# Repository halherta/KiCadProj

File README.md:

This is a Repo of some of My PCB Designs. More to follow...

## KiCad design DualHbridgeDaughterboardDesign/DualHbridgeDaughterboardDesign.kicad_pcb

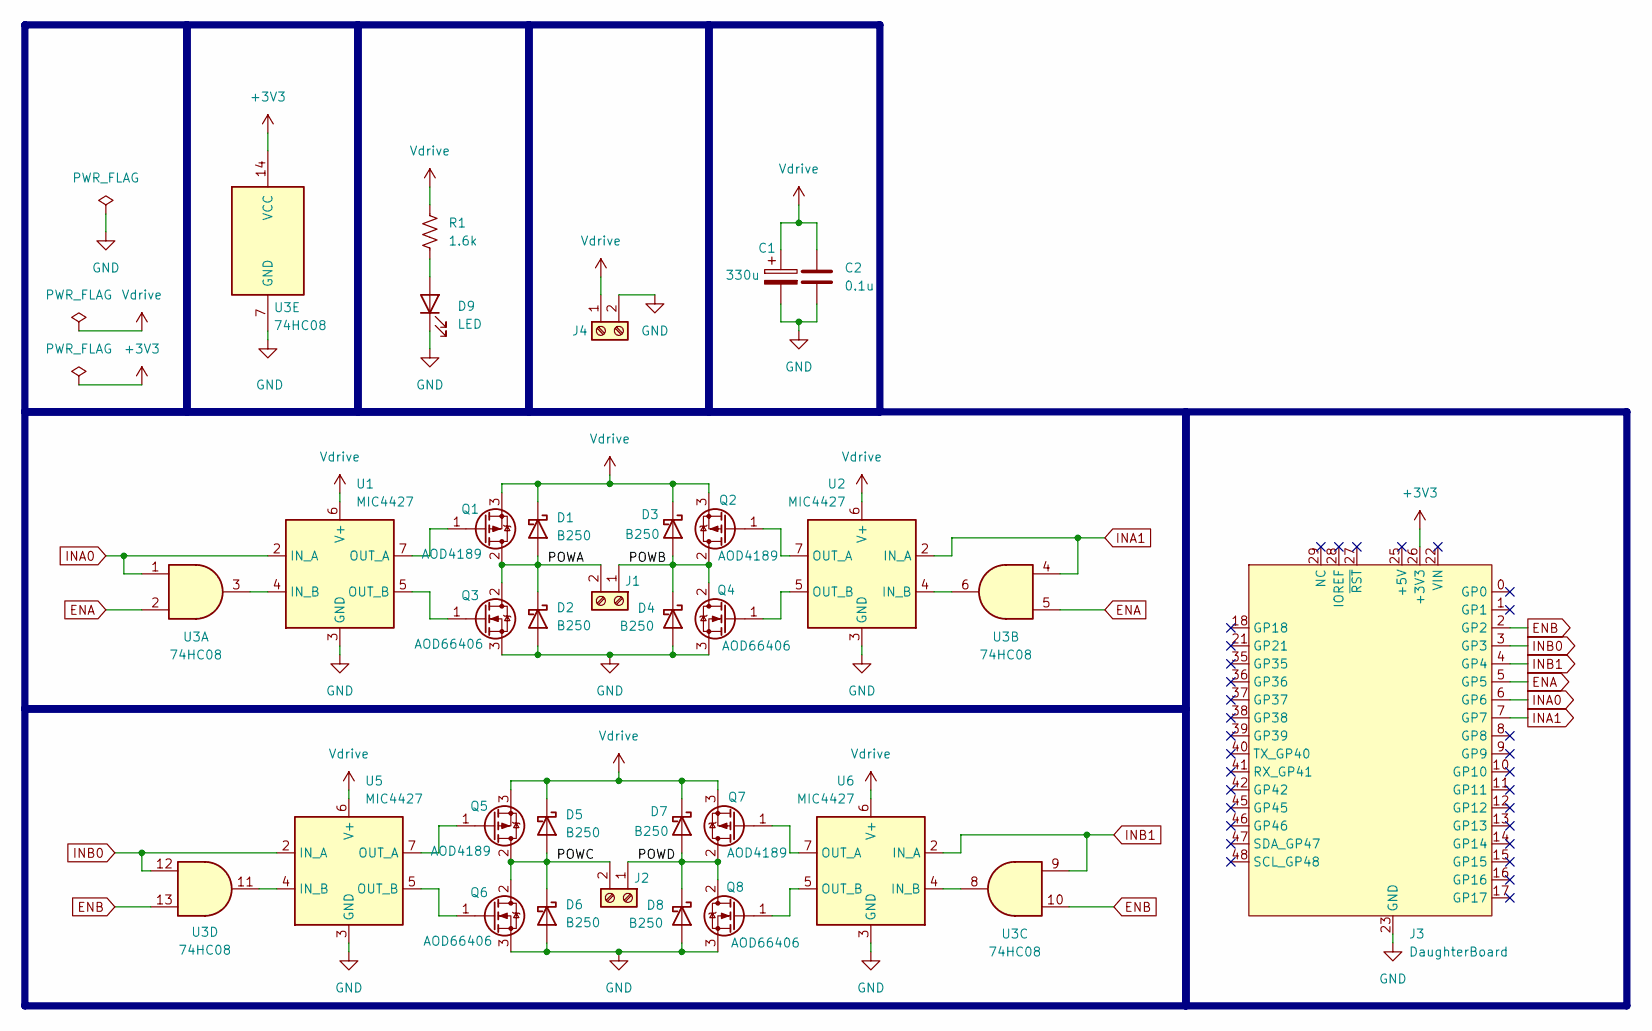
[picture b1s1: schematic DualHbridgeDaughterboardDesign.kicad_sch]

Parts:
C1: 330u; CP_Elec_8x10
C2: 0.1u; C_1206_3216Metric_Pad1.33x1.80mm_HandSolder
D1, D2, D3, D4, D5, D6, D7, D8: B250; D_SMB
D9: LED; LED_1206_3216Metric_Pad1.42x1.75mm_HandSolder
J1, J2, J4: Screw_Terminal_01x02; TerminalBlock_Altech_AK300-2_P5.00mm
J3: DaughterBoard; DaughterBoardTemplate
Q1, Q2, Q5, Q7: AOD4189; TO-252-2
Q3, Q4, Q6, Q8: AOD66406; TO-252-2
R1: 1.6k; R_1206_3216Metric_Pad1.30x1.75mm_HandSolder
U1, U2, U5, U6: MIC4427; SO-8_3.9x4.9mm_P1.27mm
U3: 74HC08; SO-14_3.9x8.65mm_P1.27mm

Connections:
+3V3: J3.26 (+3V3), J3.32 (+3V3), U3.14 (VCC)
/POWA: D1.2 (A), D2.1 (K), J1.2, Q1.2 (D), Q3.2 (D)
/POWB: D3.2 (A), D4.1 (K), J1.1, Q2.2 (D), Q4.2 (D)
/POWC: D5.2 (A), D6.1 (K), J2.2, Q5.2 (D), Q6.2 (D)
/POWD: D7.2 (A), D8.1 (K), J2.1, Q7.2 (D), Q8.2 (D)
ENA: J3.5 (GP5), U3.2, U3.5
ENB: J3.2 (GP2), U3.10, U3.13
GND: C1.2, C2.2, D2.2 (A), D4.2 (A), D6.2 (A), D8.2 (A), D9.1 (K), J3.23 (GND), J3.24 (GND), J3.30 (GND), J4.2, Q3.3 (S), Q4.3 (S), Q6.3 (S), Q8.3 (S), U1.3 (GND), U2.3 (GND), U3.7 (GND), U5.3 (GND), U6.3 (GND)
INA0: J3.6 (GP6), U1.2 (IN_A), U3.1
INA1: J3.7 (GP7), U2.2 (IN_A), U3.4
INB0: J3.3 (GP3), U3.12, U5.2 (IN_A)
INB1: J3.4 (GP4), U3.9, U6.2 (IN_A)
unnamed: D9.2 (A), R1.2
unnamed: Q1.1 (G), U1.7 (OUT_A)
unnamed: Q2.1 (G), U2.7 (OUT_A)
unnamed: Q3.1 (G), U1.5 (OUT_B)
unnamed: Q4.1 (G), U2.5 (OUT_B)
unnamed: Q5.1 (G), U5.7 (OUT_A)
unnamed: Q6.1 (G), U5.5 (OUT_B)
unnamed: Q7.1 (G), U6.7 (OUT_A)
unnamed: Q8.1 (G), U6.5 (OUT_B)
unnamed: U1.4 (IN_B), U3.3
unnamed: U2.4 (IN_B), U3.6
unnamed: U3.11, U5.4 (IN_B)
unnamed: U3.8, U6.4 (IN_B)
Vdrive: C1.1, C2.1, D1.1 (K), D3.1 (K), D5.1 (K), D7.1 (K), J4.1, Q1.3 (S), Q2.3 (S), Q5.3 (S), Q7.3 (S), R1.1, U1.6 (V+), U2.6 (V+), U5.6 (V+), U6.6 (V+)

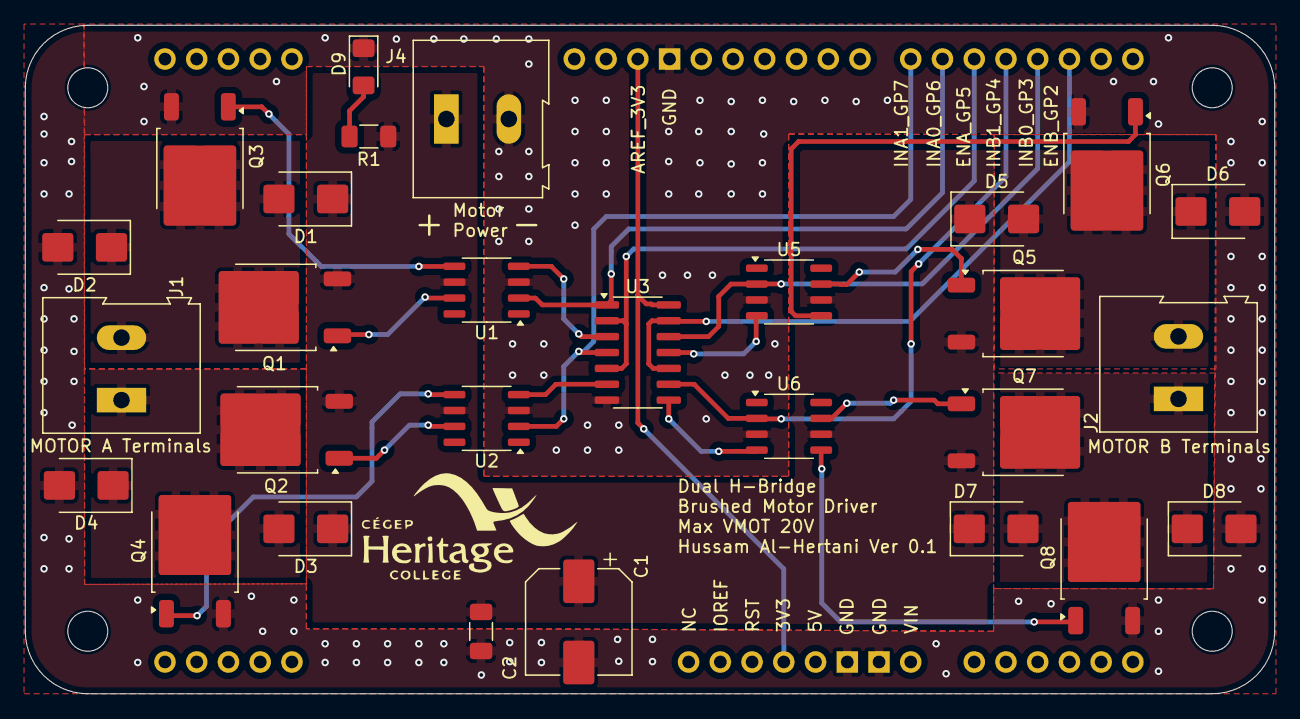
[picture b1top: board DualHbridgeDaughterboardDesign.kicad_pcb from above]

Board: 2 copper layers, 100.0 x 53.5 mm, 29 parts (0 on the bottom side), 26 nets.

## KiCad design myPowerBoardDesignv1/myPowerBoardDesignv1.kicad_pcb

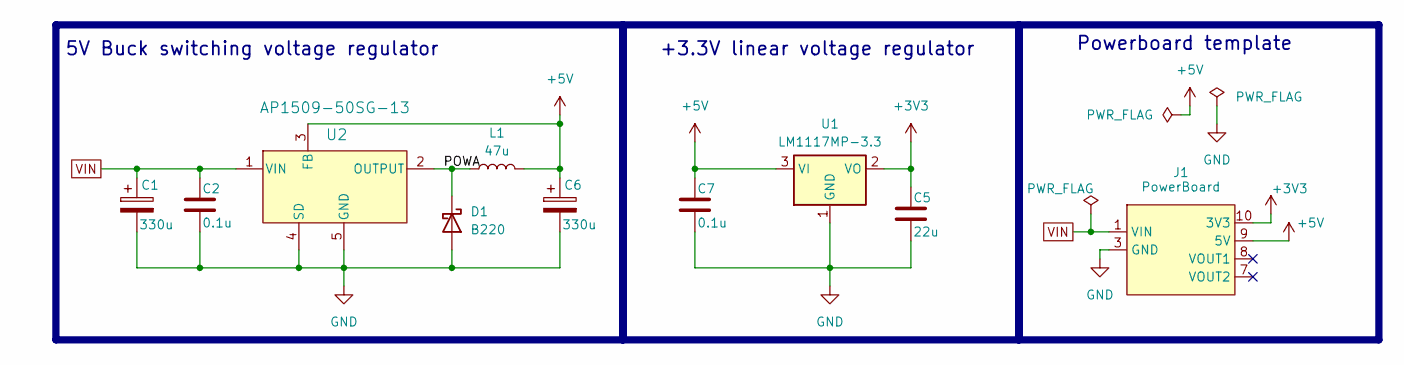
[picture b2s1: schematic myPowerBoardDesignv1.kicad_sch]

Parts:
C1, C6: 330u; CP_Elec_8x10.5
C2, C7: 0.1u; C_1206_3216Metric_Pad1.33x1.80mm_HandSolder
C5: 22u; C_1206_3216Metric_Pad1.33x1.80mm_HandSolder
D1: B220; D_SMB
J1: PowerBoard; PowerBoardTemplate
L1: 47u; L_Bourns-SRN1060
U1: LM1117MP-3.3; SOT-223-3_TabPin2
U2: AP1509-50SG-13; SOP-8_3.9x4.9mm_P1.27mm

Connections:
+3V3: C5.2, J1.10 (3V3), U1.2 (VO)
+5V: C6.1, C7.2, J1.9 (5V), L1.2, U1.3 (VI), U2.3 (FB)
/POWA: D1.1 (K), L1.1, U2.2 (OUTPUT)
GND: C1.2, C2.1, C5.1, C6.2, C7.1, D1.2 (A), J1.3 (GND), J1.4 (GND), J1.5 (GND), J1.6 (GND), U1.1 (GND), U2.4 (SD), U2.5 (GND), U2.6 (GND), U2.7 (GND), U2.8 (GND)
VIN: C1.1, C2.2, J1.1 (VIN), J1.2 (VIN), U2.1 (VIN)

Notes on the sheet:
5V Buck switching voltage regulator
Powerboard template
+3.3V linear voltage regulator

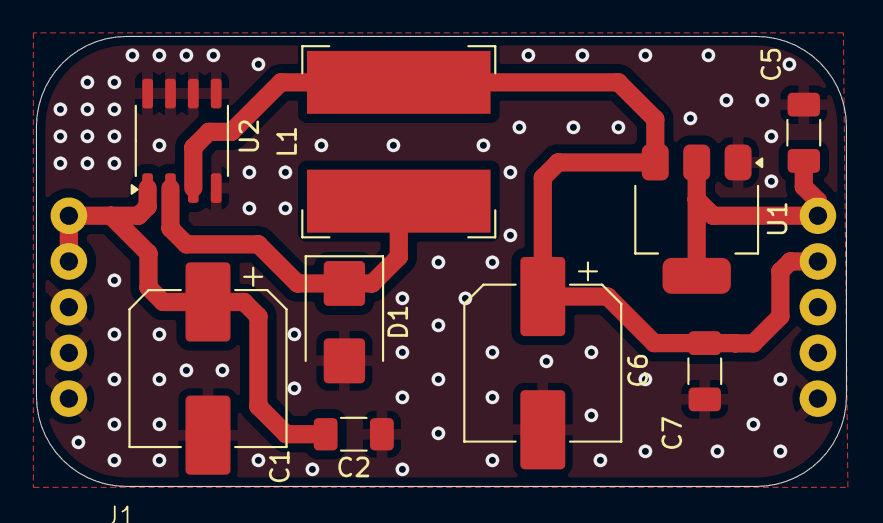
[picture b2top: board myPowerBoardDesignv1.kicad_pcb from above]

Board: 2 copper layers, 45.0 x 25.0 mm, 10 parts (0 on the bottom side), 5 nets.

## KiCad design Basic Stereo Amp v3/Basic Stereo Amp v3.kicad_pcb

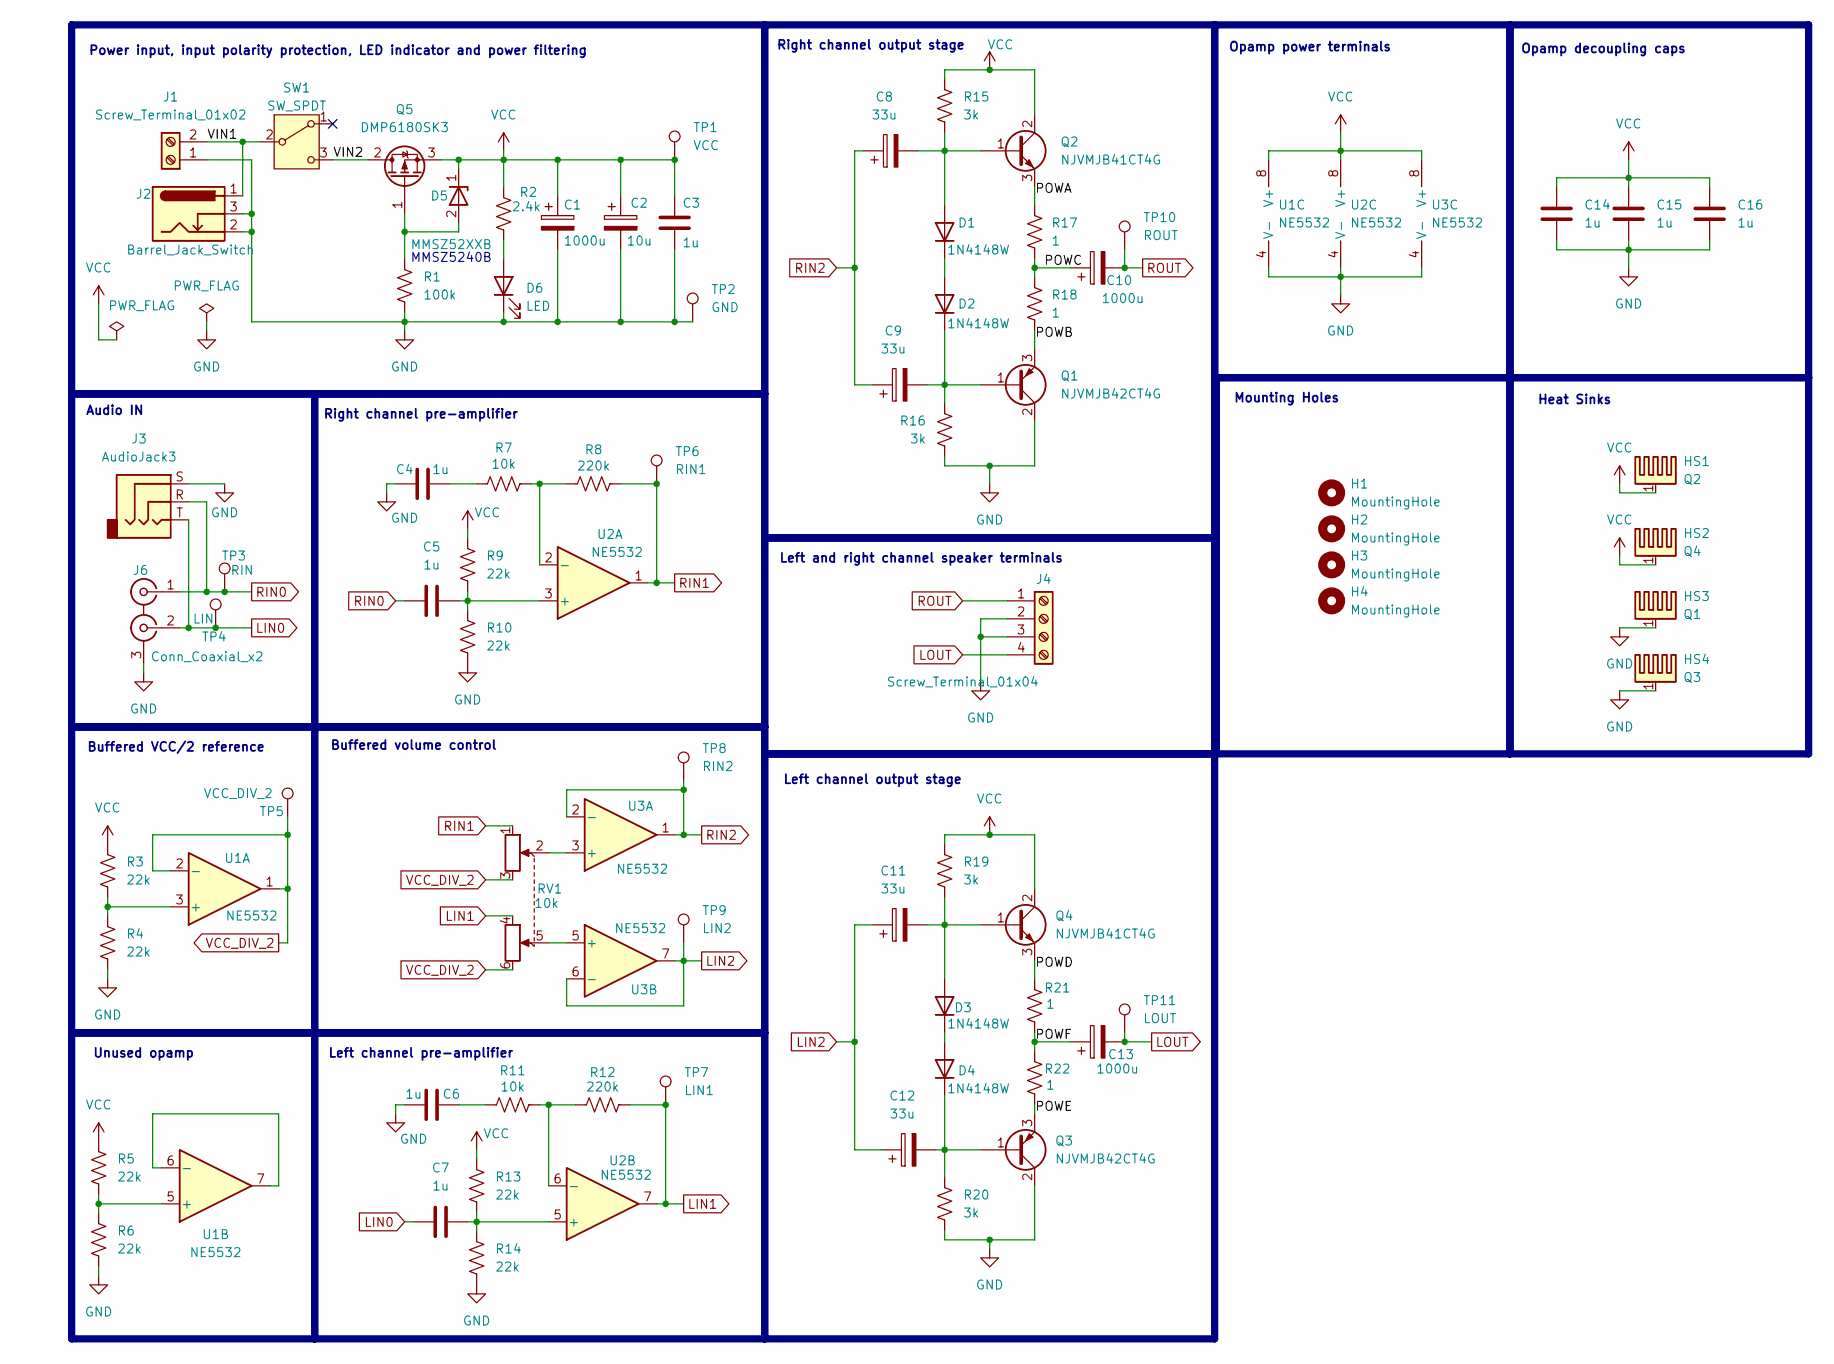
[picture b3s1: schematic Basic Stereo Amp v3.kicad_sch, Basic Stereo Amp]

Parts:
C1, C10, C13: 1000u; CP_Elec_16x17.5
C2: 10u; CP_Elec_5x5.3
C3, C4, C5, C6, C7, C14, C15, C16: 1u; C_1206_3216Metric_Pad1.33x1.80mm_HandSolder
C8, C9, C11, C12: 33u; C_Elec_6.3x5.4
D1, D2, D3, D4: 1N4148W; D_SOD-123
D5: MMSZ52XXB; D_SOD-123
D6: LED; LED_1206_3216Metric_Pad1.42x1.75mm_HandSolder
H1, H2, H3, H4: MountingHole; MountingHole_3.2mm_M3_ISO7380
HS1: Q2; Heatsink_AAVID_573300D00010G_TO-263
HS2: Q4; Heatsink_AAVID_573300D00010G_TO-263
HS3: Q1; Heatsink_AAVID_573300D00010G_TO-263
HS4: Q3; Heatsink_AAVID_573300D00010G_TO-263
J1: Screw_Terminal_01x02; TerminalBlock_Altech_AK300-2_P5.00mm
J2: Barrel_Jack_Switch; BarrelJack_CUI_PJ-102AH_Horizontal
J3: AudioJack3; Jack_3.5mm_CUI_SJ1-3533NG_Horizontal
J4: Screw_Terminal_01x04; TerminalBlock_Altech_AK300-4_P5.00mm
J6: Conn_Coaxial_x2; RCJ-2223
Q1, Q3: NJVMJB42CT4G; TO-263-2
Q2, Q4: NJVMJB41CT4G; TO-263-2
Q5: DMP6180SK3; TO-252-2
R1: 100k; R_1206_3216Metric_Pad1.30x1.75mm_HandSolder
R2: 2.4k; R_1206_3216Metric_Pad1.30x1.75mm_HandSolder
R3, R4, R5, R6, R9, R10, R13, R14: 22k; R_1206_3216Metric_Pad1.30x1.75mm_HandSolder
R7, R11: 10k; R_1206_3216Metric_Pad1.30x1.75mm_HandSolder
R8, R12: 220k; R_1206_3216Metric_Pad1.30x1.75mm_HandSolder
R15, R16, R19, R20: 3k; R_1206_3216Metric_Pad1.30x1.75mm_HandSolder
R17, R18, R21, R22: 1; R_2512_6332Metric_Pad1.40x3.35mm_HandSolder
RV1: 10k; PTD902-2015K-B103
SW1: SW_SPDT; SW_E-Switch_EG1224_SPDT_Angled
TP1: VCC; TestPoint_THTPad_D2.0mm_Drill1.0mm
TP2: GND; TestPoint_THTPad_D2.0mm_Drill1.0mm
TP3: RIN; TestPoint_THTPad_D2.0mm_Drill1.0mm
TP4: LIN; TestPoint_THTPad_D2.0mm_Drill1.0mm
TP5: VCC_DIV_2; TestPoint_THTPad_D2.0mm_Drill1.0mm
TP6: RIN1; TestPoint_THTPad_D2.0mm_Drill1.0mm
TP7: LIN1; TestPoint_THTPad_D2.0mm_Drill1.0mm
TP8: RIN2; TestPoint_THTPad_D2.0mm_Drill1.0mm
TP9: LIN2; TestPoint_THTPad_D2.0mm_Drill1.0mm
TP10: ROUT; TestPoint_THTPad_D2.0mm_Drill1.0mm
TP11: LOUT; TestPoint_THTPad_D2.0mm_Drill1.0mm
U1, U2, U3: NE5532; SOIC-8_3.9x4.9mm_P1.27mm

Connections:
/POWA: Q2.3 (E), R17.1
/POWB: Q1.3 (E), R18.2
/POWC: C10.1, R17.2, R18.1
/POWD: Q4.3 (E), R21.1
/POWE: Q3.3 (E), R22.2
/POWF: C13.1, R21.2, R22.1
/VIN1: J1.2, J2.1, SW1.2 (B)
/VIN2: Q5.2 (D), SW1.3 (C)
GND: C1.2, C2.2, C3.2, C4.2, C6.2, C14.2, C15.2, C16.2, D6.1 (K), HS3.1, HS4.1, J1.1, J2.2, J2.3, J3.S, J4.2, J4.3, J6.3 (EXT), Q1.2 (C), Q3.2 (C), R1.2, R4.1, R6.1, R10.1, R14.1, R16.2, R20.2, TP2.1, U1.4 (V-), U2.4 (V-), U3.4 (V-)
LIN0: C7.2, J3.T, J6.2 (IN2), TP4.1
LIN1: R12.2, RV1.4, TP7.1, U2.7
LIN2: C11.1, C12.1, TP9.1, U3.6 (-), U3.7
LOUT: C13.2, J4.4, TP11.1
unnamed: C4.1, R7.1
unnamed: C6.1, R11.1
unnamed: C8.2, D1.2 (A), Q2.1 (B), R15.2
unnamed: D1.1 (K), D2.2 (A)
unnamed: C9.2, D2.1 (K), Q1.1 (B), R16.1
unnamed: C11.2, D3.2 (A), Q4.1 (B), R19.2
unnamed: D3.1 (K), D4.2 (A)
unnamed: C12.2, D4.1 (K), Q3.1 (B), R20.1
unnamed: D5.2 (A), Q5.1 (G), R1.1
unnamed: D6.2 (A), R2.2
unnamed: R3.1, R4.2, U1.3 (+)
unnamed: R5.1, R6.2, U1.5 (+)
unnamed: U1.6 (-), U1.7
unnamed: C5.1, R9.1, R10.2, U2.3 (+)
unnamed: R7.2, R8.1, U2.2 (-)
unnamed: C7.1, R13.1, R14.2, U2.5 (+)
unnamed: R11.2, R12.1, U2.6 (-)
unnamed: RV1.2, U3.3 (+)
unnamed: RV1.5, U3.5 (+)
RIN0: C5.2, J3.R, J6.1 (IN1), TP3.1
RIN1: R8.2, RV1.1, TP6.1, U2.1
RIN2: C8.1, C9.1, TP8.1, U3.1, U3.2 (-)
ROUT: C10.2, J4.1, TP10.1
VCC: C1.1, C2.1, C3.1, C14.1, C15.1, C16.1, D5.1 (K), HS1.1, HS2.1, Q2.2 (C), Q4.2 (C), Q5.3 (S), R2.1, R3.2, R5.2, R9.2, R13.2, R15.1, R19.1, TP1.1, U1.8 (V+), U2.8 (V+), U3.8 (V+)
VCC_DIV_2: RV1.3, RV1.6, TP5.1, U1.1, U1.2 (-)

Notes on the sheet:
Left channel output stage
Audio IN
MMSZ5240B
Heat Sinks
Opamp decoupling caps
Mounting Holes
Buffered volume control
Opamp power terminals
Right channel pre-amplifier
Buffered VCC/2 reference
Unused opamp
Right channel output stage
Left and right channel speaker terminals
Left channel pre-amplifier
Power input, input polarity protection, LED indicator and power filtering

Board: 2 copper layers, 78 parts (0 on the bottom side), 38 nets, no tracks yet.

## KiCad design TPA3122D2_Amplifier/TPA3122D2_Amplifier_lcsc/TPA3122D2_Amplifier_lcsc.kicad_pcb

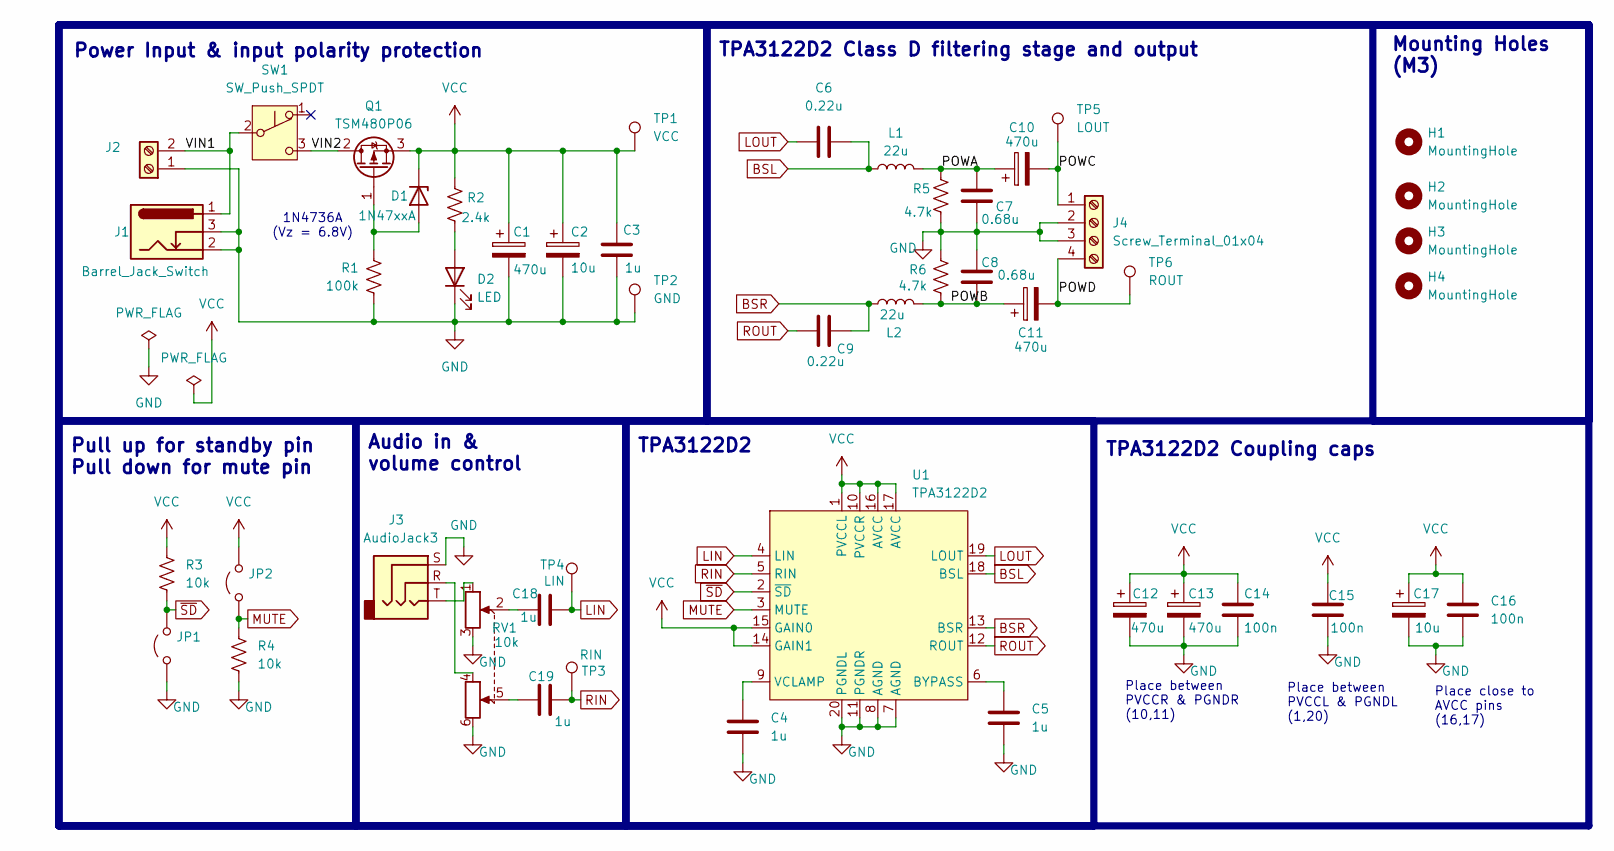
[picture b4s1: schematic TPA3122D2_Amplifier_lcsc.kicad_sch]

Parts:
C1, C10, C11, C12, C13: 470u; CP_Radial_D10.0mm_P5.00mm
C2, C17: 10u; CP_Radial_D5.0mm_P2.50mm
C3, C4, C5, C18, C19: 1u; C_Disc_D4.3mm_W1.9mm_P5.00mm
C6, C9: 0.22u; C_Disc_D4.3mm_W1.9mm_P5.00mm
C7, C8: 0.68u; C_Disc_D4.3mm_W1.9mm_P5.00mm
C14, C15, C16: 100n; C_Disc_D4.3mm_W1.9mm_P5.00mm
D1: 1N47xxA; D_DO-41_SOD81_P10.16mm_Horizontal
D2: LED; LED_D5.0mm
H1, H2, H3, H4: MountingHole; MountingHole_3.2mm_M3
J1: Barrel_Jack_Switch; BarrelJack_CUI_PJ-102AH_Horizontal
J2: Screw_Terminal_01x02; TerminalBlock_Altech_AK300-2_P5.00mm
J3: AudioJack3; Jack_3.5mm_CUI_SJ1-3533NG_Horizontal
J4: Screw_Terminal_01x04; TerminalBlock_Altech_AK300-4_P5.00mm
JP1, JP2: Jumper_2_Open; PinHeader_1x02_P2.54mm_Vertical
L1, L2: 22u; L_Radial_D10.0mm_P5.00mm_Fastron_07M
Q1: TSM480P06; TO-251-3_Vertical
R1: 100k; R_Axial_DIN0207_L6.3mm_D2.5mm_P10.16mm_Horizontal
R2: 2.4k; R_Axial_DIN0207_L6.3mm_D2.5mm_P10.16mm_Horizontal
R3, R4: 10k; R_Axial_DIN0207_L6.3mm_D2.5mm_P10.16mm_Horizontal
R5, R6: 4.7k; R_Axial_DIN0207_L6.3mm_D2.5mm_P10.16mm_Horizontal
RV1: 10k; PTD902-2015K-B103
SW1: SW_Push_SPDT; SW_E-Switch_EG1224_SPDT_Angled
TP1: VCC; TestPoint_THTPad_D2.0mm_Drill1.0mm
TP2: GND; TestPoint_THTPad_D2.0mm_Drill1.0mm
TP3: RIN; TestPoint_THTPad_D2.0mm_Drill1.0mm
TP4: LIN; TestPoint_THTPad_D2.0mm_Drill1.0mm
TP5: LOUT; TestPoint_THTPad_D2.0mm_Drill1.0mm
TP6: ROUT; TestPoint_THTPad_D2.0mm_Drill1.0mm
U1: TPA3122D2; DIP-20_W7.62mm_LongPads

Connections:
/POWA: C7.1, C10.1, L1.2, R5.1
/POWB: C8.2, C11.1, L2.2, R6.2
/POWC: C10.2, J4.1, TP5.1
/POWD: C11.2, J4.4, TP6.1
/VIN1: J1.1, J2.2, SW1.2 (B)
/VIN2: Q1.2 (D), SW1.3 (C)
BSL: C6.1, L1.1, U1.18 (BSL)
BSR: C9.1, L2.1, U1.13 (BSR)
GND: C1.2, C2.2, C3.2, C4.2, C5.2, C7.2, C8.1, C12.2, C13.2, C14.2, C15.2, C16.2, C17.2, D2.1 (K), J1.2, J1.3, J2.1, J3.S, J4.2, J4.3, JP1.1 (A), R1.2, R4.2, R5.2, R6.1, RV1.3, RV1.6, TP2.1, U1.7 (AGND), U1.8 (AGND), U1.11 (PGNDR), U1.20 (PGNDL)
LIN: C18.2, TP4.1, U1.4 (LIN)
LOUT: C6.2, U1.19 (LOUT)
MUTE: JP2.1 (A), R4.1, U1.3 (MUTE)
unnamed: C18.1, RV1.2
unnamed: C19.1, RV1.5
unnamed: D1.2 (A), Q1.1 (G), R1.1
unnamed: D2.2 (A), R2.2
unnamed: J3.R, RV1.4
unnamed: J3.T, RV1.1
unnamed: C5.1, U1.6 (BYPASS)
unnamed: C4.1, U1.9 (VCLAMP)
RIN: C19.2, TP3.1, U1.5 (RIN)
ROUT: C9.2, U1.12 (ROUT)
VCC: C1.1, C2.1, C3.1, C12.1, C13.1, C14.1, C15.1, C16.1, C17.1, D1.1 (K), JP2.2 (B), Q1.3 (S), R2.1, R3.1, TP1.1, U1.1 (PVCCL), U1.10 (PVCCR), U1.14 (GAIN1), U1.15 (GAIN0), U1.16 (AVCC), U1.17 (AVCC)
~SD: JP1.2 (B), R3.2, U1.2 (~SD)

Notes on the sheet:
1N4736A (Vz = 6.8V)
Audio in & volume control
Power Input & input polarity protection
TPA3122D2 Coupling caps
Mounting Holes (M3)
TPA3122D2
Place between PVCCR & PGNDR (10,11)
Place between PVCCL & PGNDL (1,20)
Place close to AVCC pins (16,17)
TPA3122D2 Class D filtering stage and output
Pull up for standby pin Pull down for mute pin

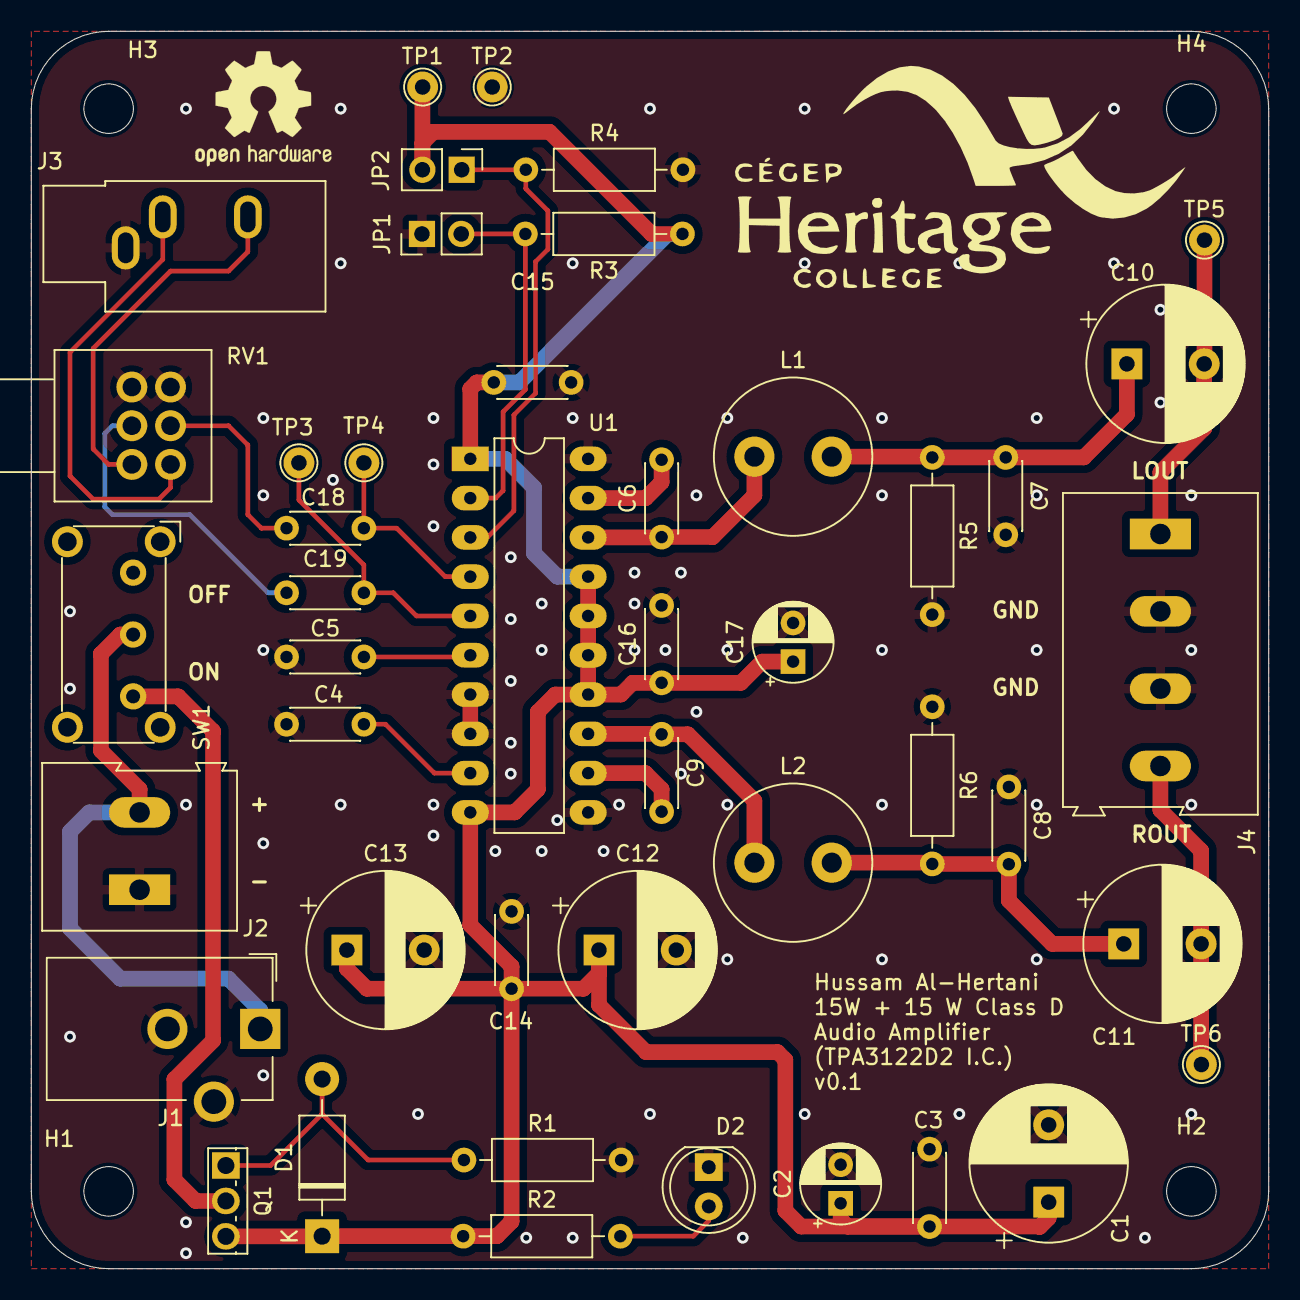
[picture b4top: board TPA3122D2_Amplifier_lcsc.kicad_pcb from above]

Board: 2 copper layers, 80.0 x 80.0 mm, 49 parts (0 on the bottom side), 24 nets.

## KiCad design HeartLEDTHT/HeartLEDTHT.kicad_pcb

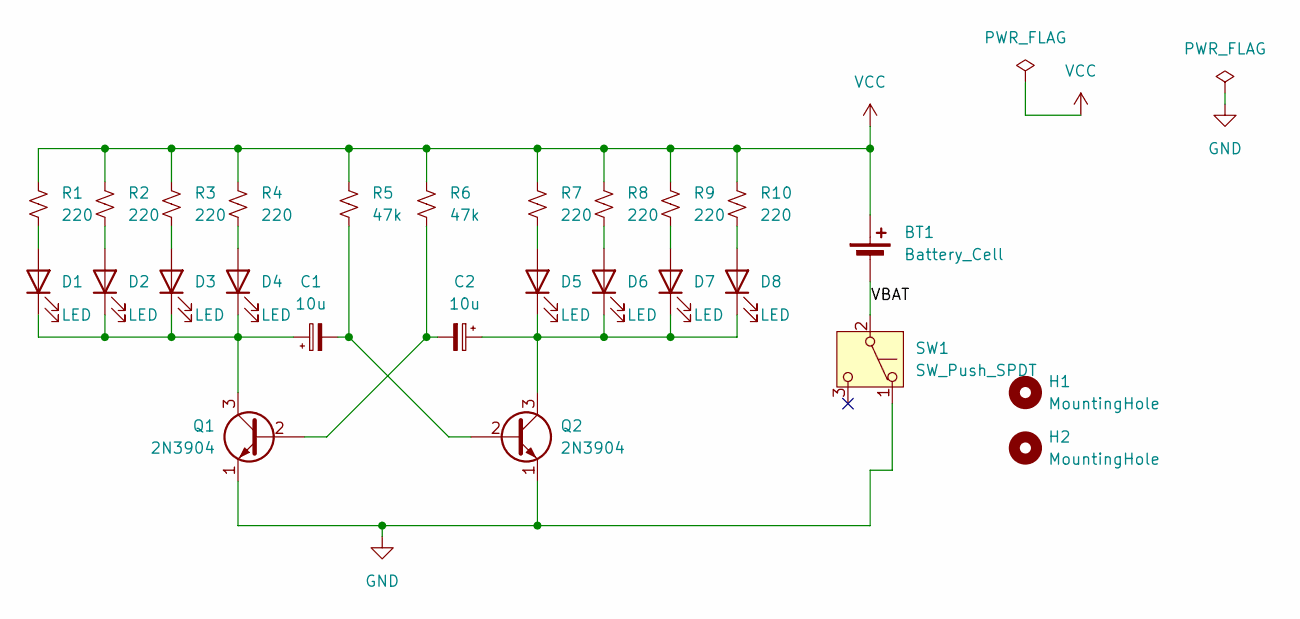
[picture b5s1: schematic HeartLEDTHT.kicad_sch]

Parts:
BT1: Battery_Cell; BatteryHolder_Keystone_3002_1x2032
C1, C2: 10u; CP_Radial_D5.0mm_P2.00mm
D1, D2, D3, D4, D5, D6, D7, D8: LED; LED_D5.0mm
H1, H2: MountingHole; MountingHole_4.3mm_M4
Q1, Q2: 2N3904; TO-92_Inline
R1, R2, R3, R4, R7, R8, R9, R10: 220; R_Axial_DIN0207_L6.3mm_D2.5mm_P10.16mm_Horizontal
R5, R6: 47k; R_Axial_DIN0207_L6.3mm_D2.5mm_P10.16mm_Horizontal
SW1: SW_Push_SPDT; SW_SPDT_CK_JS102011SAQN

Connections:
/VBAT: BT1.2 (-), SW1.2 (B)
GND: Q1.1 (E), Q2.1 (E), SW1.1 (A)
unnamed: D1.2 (A), R1.2
unnamed: C1.1, D1.1 (K), D2.1 (K), D3.1 (K), D4.1 (K), Q1.3 (C)
unnamed: D2.2 (A), R2.2
unnamed: D3.2 (A), R3.2
unnamed: D4.2 (A), R4.2
unnamed: D5.2 (A), R7.2
unnamed: C2.1, D5.1 (K), D6.1 (K), D7.1 (K), D8.1 (K), Q2.3 (C)
unnamed: D6.2 (A), R8.2
unnamed: D7.2 (A), R9.2
unnamed: D8.2 (A), R10.2
unnamed: C2.2, Q1.2 (B), R6.2
unnamed: C1.2, Q2.2 (B), R5.2
VCC: BT1.1 (+), R1.1, R2.1, R3.1, R4.1, R5.1, R6.1, R7.1, R8.1, R9.1, R10.1

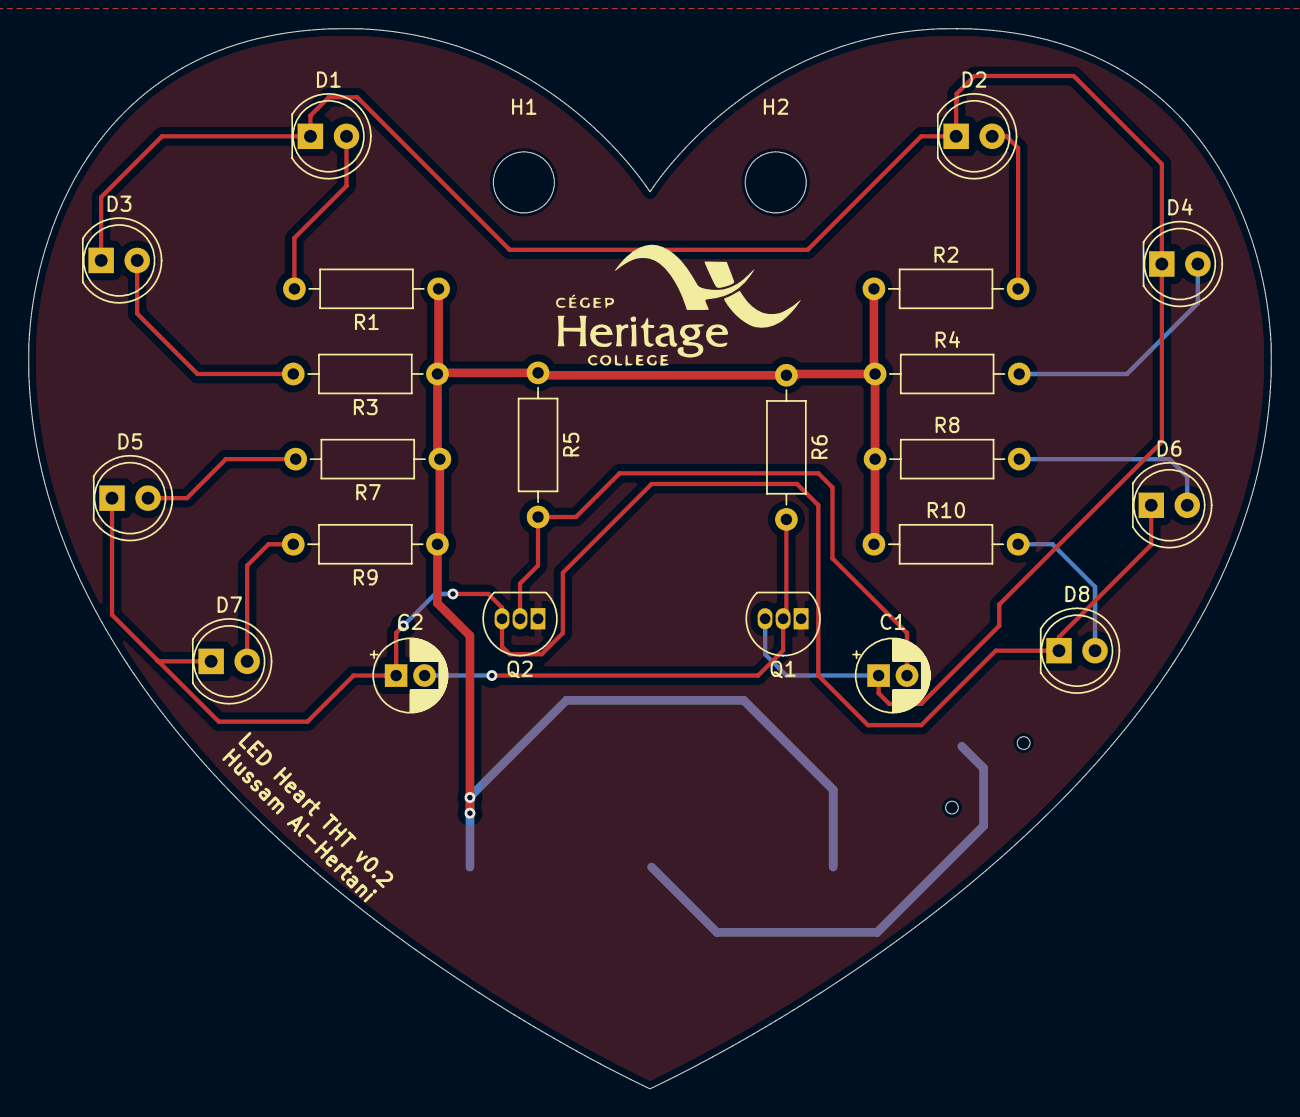
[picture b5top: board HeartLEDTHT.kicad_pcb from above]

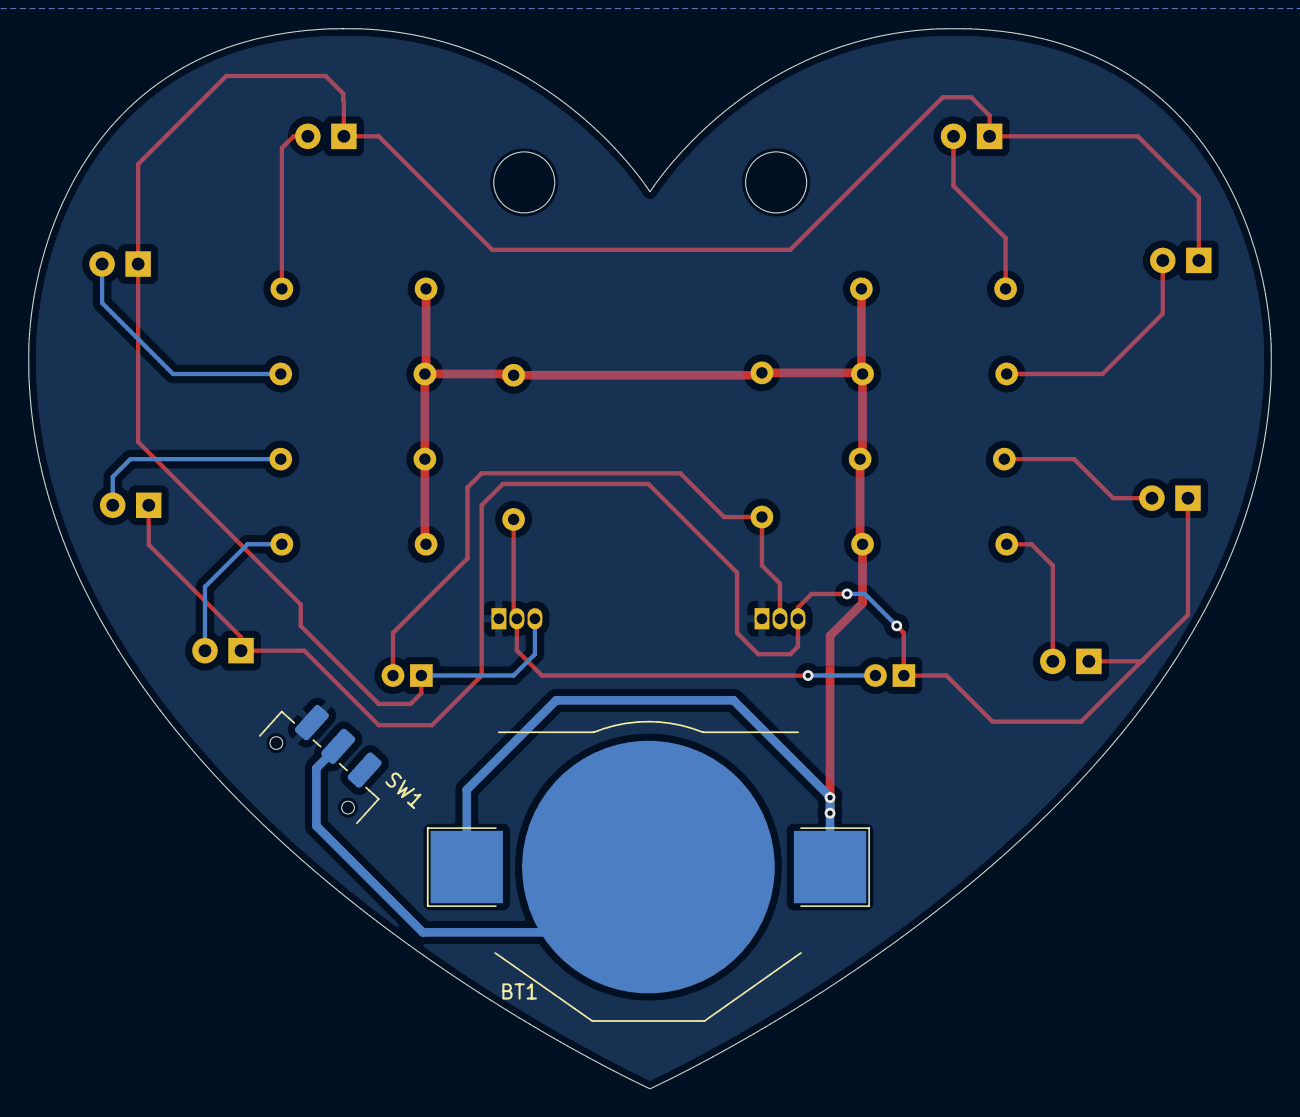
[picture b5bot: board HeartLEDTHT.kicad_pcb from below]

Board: 2 copper layers, 87.6 x 74.7 mm, 26 parts (2 on the bottom side), 15 nets.

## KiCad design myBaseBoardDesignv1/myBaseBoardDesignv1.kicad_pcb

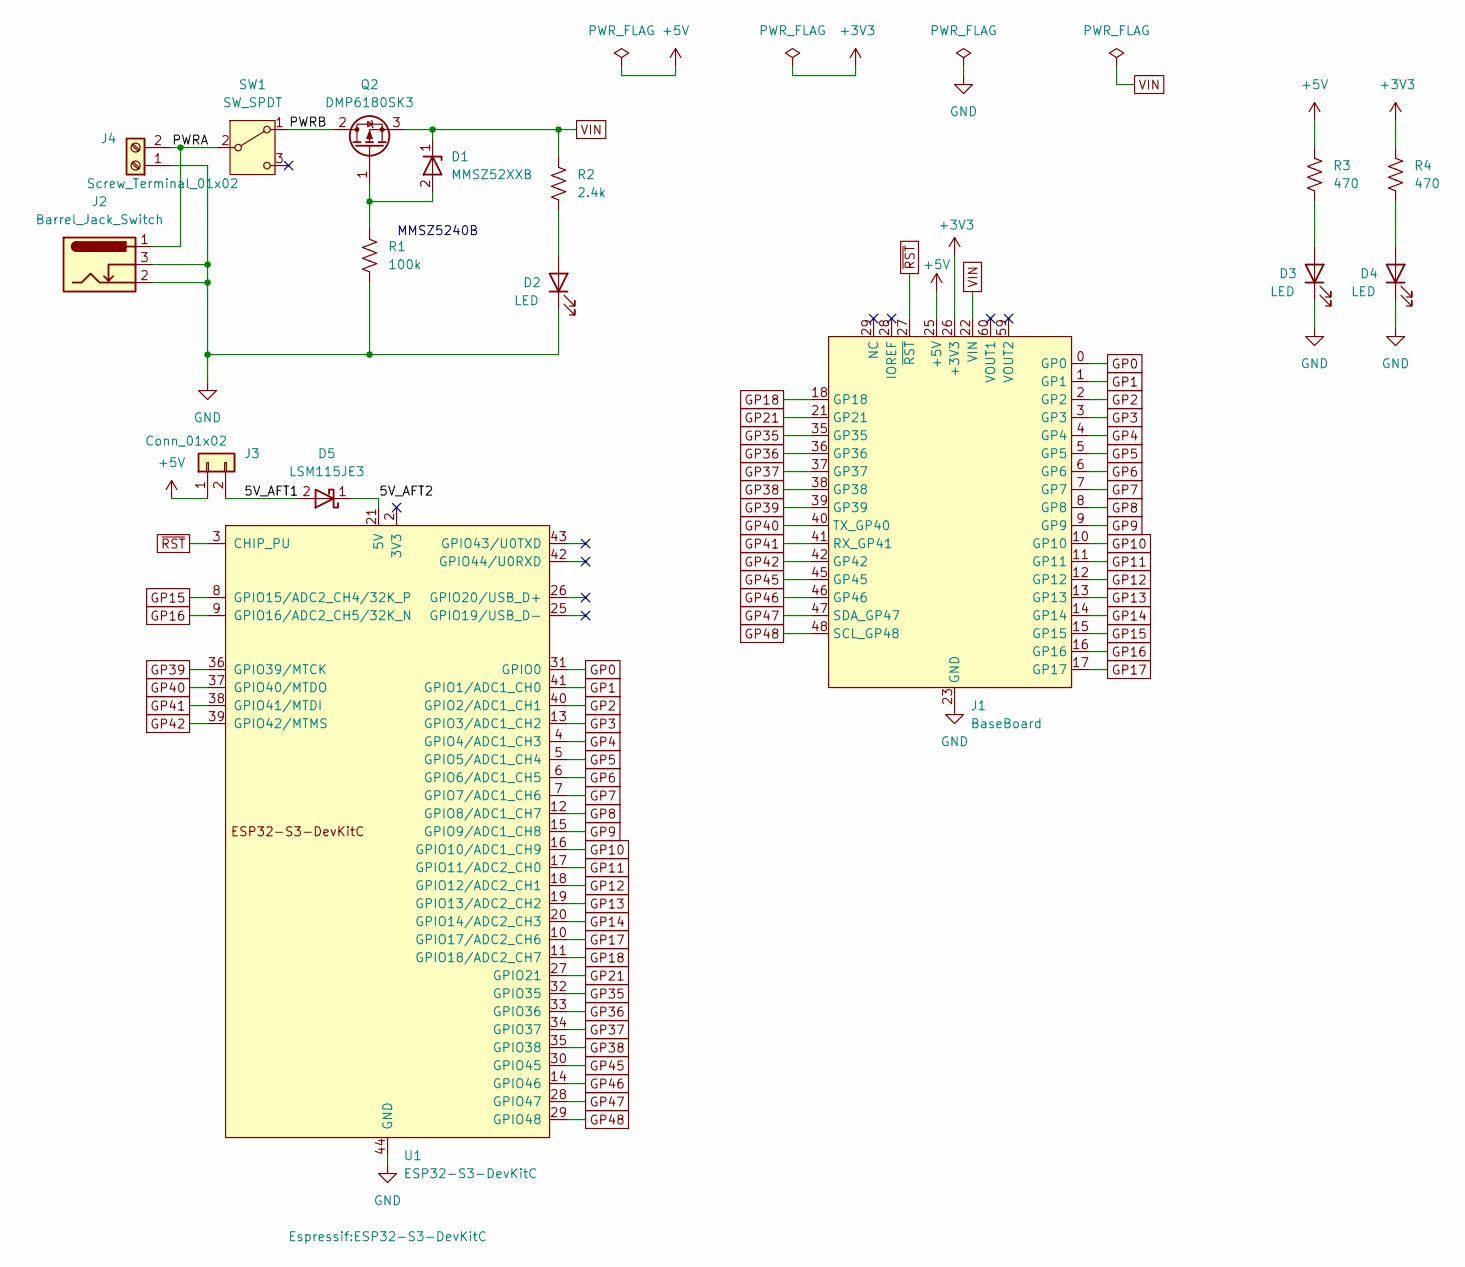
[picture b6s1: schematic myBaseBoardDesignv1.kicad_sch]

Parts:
D1: MMSZ52XXB; D_SOD-123
D2, D3, D4: LED; LED_1206_3216Metric_Pad1.42x1.75mm_HandSolder
D5: LSM115JE3; D_SMA
J1: BaseBoard; BaseBoardTemplate
J2: Barrel_Jack_Switch; BarrelJack_CUI_PJ-102AH_Horizontal
J3: Conn_01x02; PinHeader_1x02_P2.54mm_Vertical
J4: Screw_Terminal_01x02; TerminalBlock_Altech_AK300-2_P5.00mm
Q2: DMP6180SK3; TO-252-2
R1: 100k; R_1206_3216Metric_Pad1.30x1.75mm_HandSolder
R2: 2.4k; R_1206_3216Metric_Pad1.30x1.75mm_HandSolder
R3, R4: 470; R_1206_3216Metric_Pad1.30x1.75mm_HandSolder
SW1: SW_SPDT; SW_E-Switch_EG1224_SPDT_Angled
U1: ESP32-S3-DevKitC

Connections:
+3V3: J1.26 (+3V3), J1.32 (+3V3), J1.62 (+3V3), R4.1
+5V: J1.25 (+5V), J1.61 (+5V), J3.1, R3.1
/5V_AFT1: D5.2 (A), J3.2
/5V_AFT2: D5.1 (K), U1.21 (5V)
/PWRA: J2.1, J4.2, SW1.2 (B)
/PWRB: Q2.2 (D), SW1.1 (A)
GND: D2.1 (K), D3.1 (K), D4.1 (K), J1.23 (GND), J1.24 (GND), J1.30 (GND), J1.55 (GND), J1.56 (GND), J1.57 (GND), J1.58 (GND), J2.2, J2.3, J4.1, R1.2, U1.22 (GND), U1.23 (GND), U1.24 (GND), U1.44 (GND)
GP0: J1.0 (GP0), U1.31 (GPIO0)
GP1: J1.1 (GP1), U1.41 (GPIO1/ADC1_CH0)
GP2: J1.2 (GP2), U1.40 (GPIO2/ADC1_CH1)
GP3: J1.3 (GP3), U1.13 (GPIO3/ADC1_CH2)
GP4: J1.4 (GP4), U1.4 (GPIO4/ADC1_CH3)
GP5: J1.5 (GP5), U1.5 (GPIO5/ADC1_CH4)
GP6: J1.6 (GP6), U1.6 (GPIO6/ADC1_CH5)
GP7: J1.7 (GP7), U1.7 (GPIO7/ADC1_CH6)
GP8: J1.8 (GP8), U1.12 (GPIO8/ADC1_CH7)
GP9: J1.9 (GP9), U1.15 (GPIO9/ADC1_CH8)
GP10: J1.10 (GP10), U1.16 (GPIO10/ADC1_CH9)
GP11: J1.11 (GP11), U1.17 (GPIO11/ADC2_CH0)
GP12: J1.12 (GP12), U1.18 (GPIO12/ADC2_CH1)
GP13: J1.13 (GP13), U1.19 (GPIO13/ADC2_CH2)
GP14: J1.14 (GP14), U1.20 (GPIO14/ADC2_CH3)
GP15: J1.15 (GP15), U1.8 (GPIO15/ADC2_CH4/32K_P)
GP16: J1.16 (GP16), U1.9 (GPIO16/ADC2_CH5/32K_N)
GP17: J1.17 (GP17), U1.10 (GPIO17/ADC2_CH6)
GP18: J1.18 (GP18), U1.11 (GPIO18/ADC2_CH7)
GP21: J1.21 (GP21), U1.27 (GPIO21)
GP35: J1.35 (GP35), U1.32 (GPIO35)
GP36: J1.36 (GP36), U1.33 (GPIO36)
GP37: J1.37 (GP37), U1.34 (GPIO37)
GP38: J1.38 (GP38), U1.35 (GPIO38)
GP39: J1.39 (GP39), U1.36 (GPIO39/MTCK)
GP40: J1.40 (TX_GP40), U1.37 (GPIO40/MTDO)
GP41: J1.41 (RX_GP41), U1.38 (GPIO41/MTDI)
GP42: J1.42 (GP42), U1.39 (GPIO42/MTMS)
GP45: J1.45 (GP45), U1.30 (GPIO45)
GP46: J1.46 (GP46), U1.14 (GPIO46)
GP47: J1.47 (SDA_GP47), U1.28 (GPIO47)
GP48: J1.48 (SCL_GP48), U1.29 (GPIO48)
unnamed: D1.2 (A), Q2.1 (G), R1.1
unnamed: D2.2 (A), R2.2
unnamed: D3.2 (A), R3.2
unnamed: D4.2 (A), R4.2
VIN: D1.1 (K), J1.22 (VIN), J1.53 (VIN), J1.54 (VIN), Q2.3 (S), R2.1
~RST: J1.27 (~RST), U1.3 (CHIP_PU)

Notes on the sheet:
MMSZ5240B
